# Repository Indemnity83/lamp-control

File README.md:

# ESPHome Reading Lamp (Lamp Control)

This project is a custom **ESP8266 (ESP-12E) + ESPHome retrofit** for a standard touch‑controlled bedside reading lamp, adding full **Wi‑Fi control and Home Assistant integration**.

Originally built for a fun (and slightly devious) bedtime automation, it’s now a clean, reusable **smart‑lamp controller** with both **open hardware** and **open firmware**.

Same lamp on the outside.  
Entirely new personality on the inside.

---

## ✨ Features

- ESP8266 / ESP‑12E based Wi‑Fi control  
- ESPHome firmware  
- Home Assistant native API integration  
- Smooth transitions and dimming  
- Designed to replace a stock capacitive touch controller  
- Brightness memory across power loss  
- Physical touch control + full network control

---

## 🗂️ Repository Structure

- `firmware/` – ESPHome configuration and device logic  
- `hardware/` – KiCad schematic, PCB, and mechanical assets  
- `docs/` – Rendered schematic and board images

---

## 🧠 Hardware Overview

The controller is built around a simple, low‑voltage architecture composed of four primary building blocks:

1. **Micro — ESP8266 Wi‑Fi Module (ESP‑12E)**  
   Provides all network connectivity, ESPHome firmware execution, and integration with Home Assistant.

2. **Mosfet — BSS138 MOSFET‑Based DC Dimmer Stage**  
   Handles low‑side PWM dimming of the 12V lamp load in a safe, fully low‑voltage design (no mains switching).

3. **Power — AMS1117‑3.3 Linear Voltage Regulator**  
   Steps the incoming 12V DC down to a stable 3.3V rail for the ESP8266 and logic circuitry.

4. **Touch — TTP223 Capacitive Touch Sensor**  
   Provides the physical touch interface for on/off control and brightness stepping without any mechanical switches.

### Schematic

### PCB Render

---

## 🏭 Manufacturing Assets

All fabrication outputs are generated from KiCad using the supplied Makefile:

```sh
make build
```

This generates, into the `hardware/build/` directory:

- Gerber files  
- Drill files  
- BOM (CSV)  
- Pick‑and‑place  
- PDF schematic

Manufacturing assets are also published as **GitHub Releases** and workflow artifacts.

### 🟣 Order a Pre‑Fab PCB (OSH Park)

If you prefer to skip fabrication setup and order the board directly, the exact PCB is available as a shared OSH Park project:

https://oshpark.com/shared_projects/FYbiIZpP

---

## 🧰 Bill of Materials (BOM) — Summary

This project retrofits a **touch‑controlled 12V DC bedside reading lamp** with a custom ESP8266 controller.

### 🪔 Base Lamp

- Touch‑control bedside reading lamp (original retail unit)  
- Any similar **12V capacitive‑touch lamp with an internal controller** can be adapted; however, the **PCB outline and mounting points are specifically designed for [this exact lamp model](https://a.co/d/2ksPzuO)**

> ⚠️ **USB Charging Port Note**  
> The original lamp’s built-in USB charging port will be **non-functional after this retrofit**. Supporting a protected 5V USB output (with proper current limiting and fault protection) was intentionally left **out of scope** to keep the board simple and safe.  
>  
> If you would like to restore USB charging, the recommended approach is to use a small, dedicated **12V → 5V buck converter module** and reuse the lamp’s original USB connector:  
> 1. Install a 12V → 5V buck converter module and connect the lamp’s 12V supply to the module’s input.  
> 2. **Remove the USB connector from the buck converter module** so you can access its 5V and GND output pads directly.  
> 3. Solder the original USB wiring to the 5V and GND output pads on the buck converter module, effectively feeding the original USB jack from the new 5V supply.  
>  
> Example module: https://a.co/d/jlBtOT4

> ♻️ **Salvage & Reuse Note**  
> The **spring contact** that connects the original lamp PCB to the outer plastic touch surface is **re‑used in this design**. Be sure to **pull and transfer this spring from the original board** when installing the new controller.
> 
> You can also optionally **salvage the following components from the original lamp PCB** to reduce parts sourcing:
> - The **MOSFET** (dimmer switch)
> - The tiny **22pF capacitor** used to decouple the touch spring
> - **Reverse‑polarity protection diode** (SS14‑class)
> 
> Salvaging these parts is optional but can simplify sourcing and keep e‑waste down.

### 🧠 Core Electronics

- **U3 — ESP‑12E / ESP8266 Wi‑Fi module**
- **U4 — TTP223‑BA6 capacitive touch sensor**
- **Q2 — BSS138 MOSFET** (low‑side PWM dimming)
- **U2 — AMS1117‑3.3 voltage regulator**
- **D1 — SS14 Schottky diode** (power protection)
- Decoupling and timing capacitors (C3–C7)
- Pull‑ups and current‑limit resistors (R3–R8)

---

## 🧑‍💻 Firmware

The device firmware is written in **ESPHome** and provides:

- Touch input handling via TTP223B capacitive IC  
- Brightness stepping with persistent memory  
- Long‑press physical power‑off  
- OTA updates and Home Assistant API integration

Firmware configuration files live in:

```
firmware/
```

---

## ⚡ Typical Use Cases

- Smart bedside reading lamps  
- Bedtime automations  
- Wake‑up fade lighting  
- General ESPHome‑controlled lighting

---

## 📄 License

This project uses **dual licensing**:

- **Firmware & configuration:** MIT License  
- **Hardware designs & mechanical files:** CERN Open Hardware License v2 – Permissive (CERN‑OHL‑P)

See the respective `LICENSE.md` files for full terms.

---

## ❤️ Why This Exists

Because sometimes the right solution to:

> “They’re still reading at 10 PM…”

is:

> “Fine. We’ll let the robots handle it.”

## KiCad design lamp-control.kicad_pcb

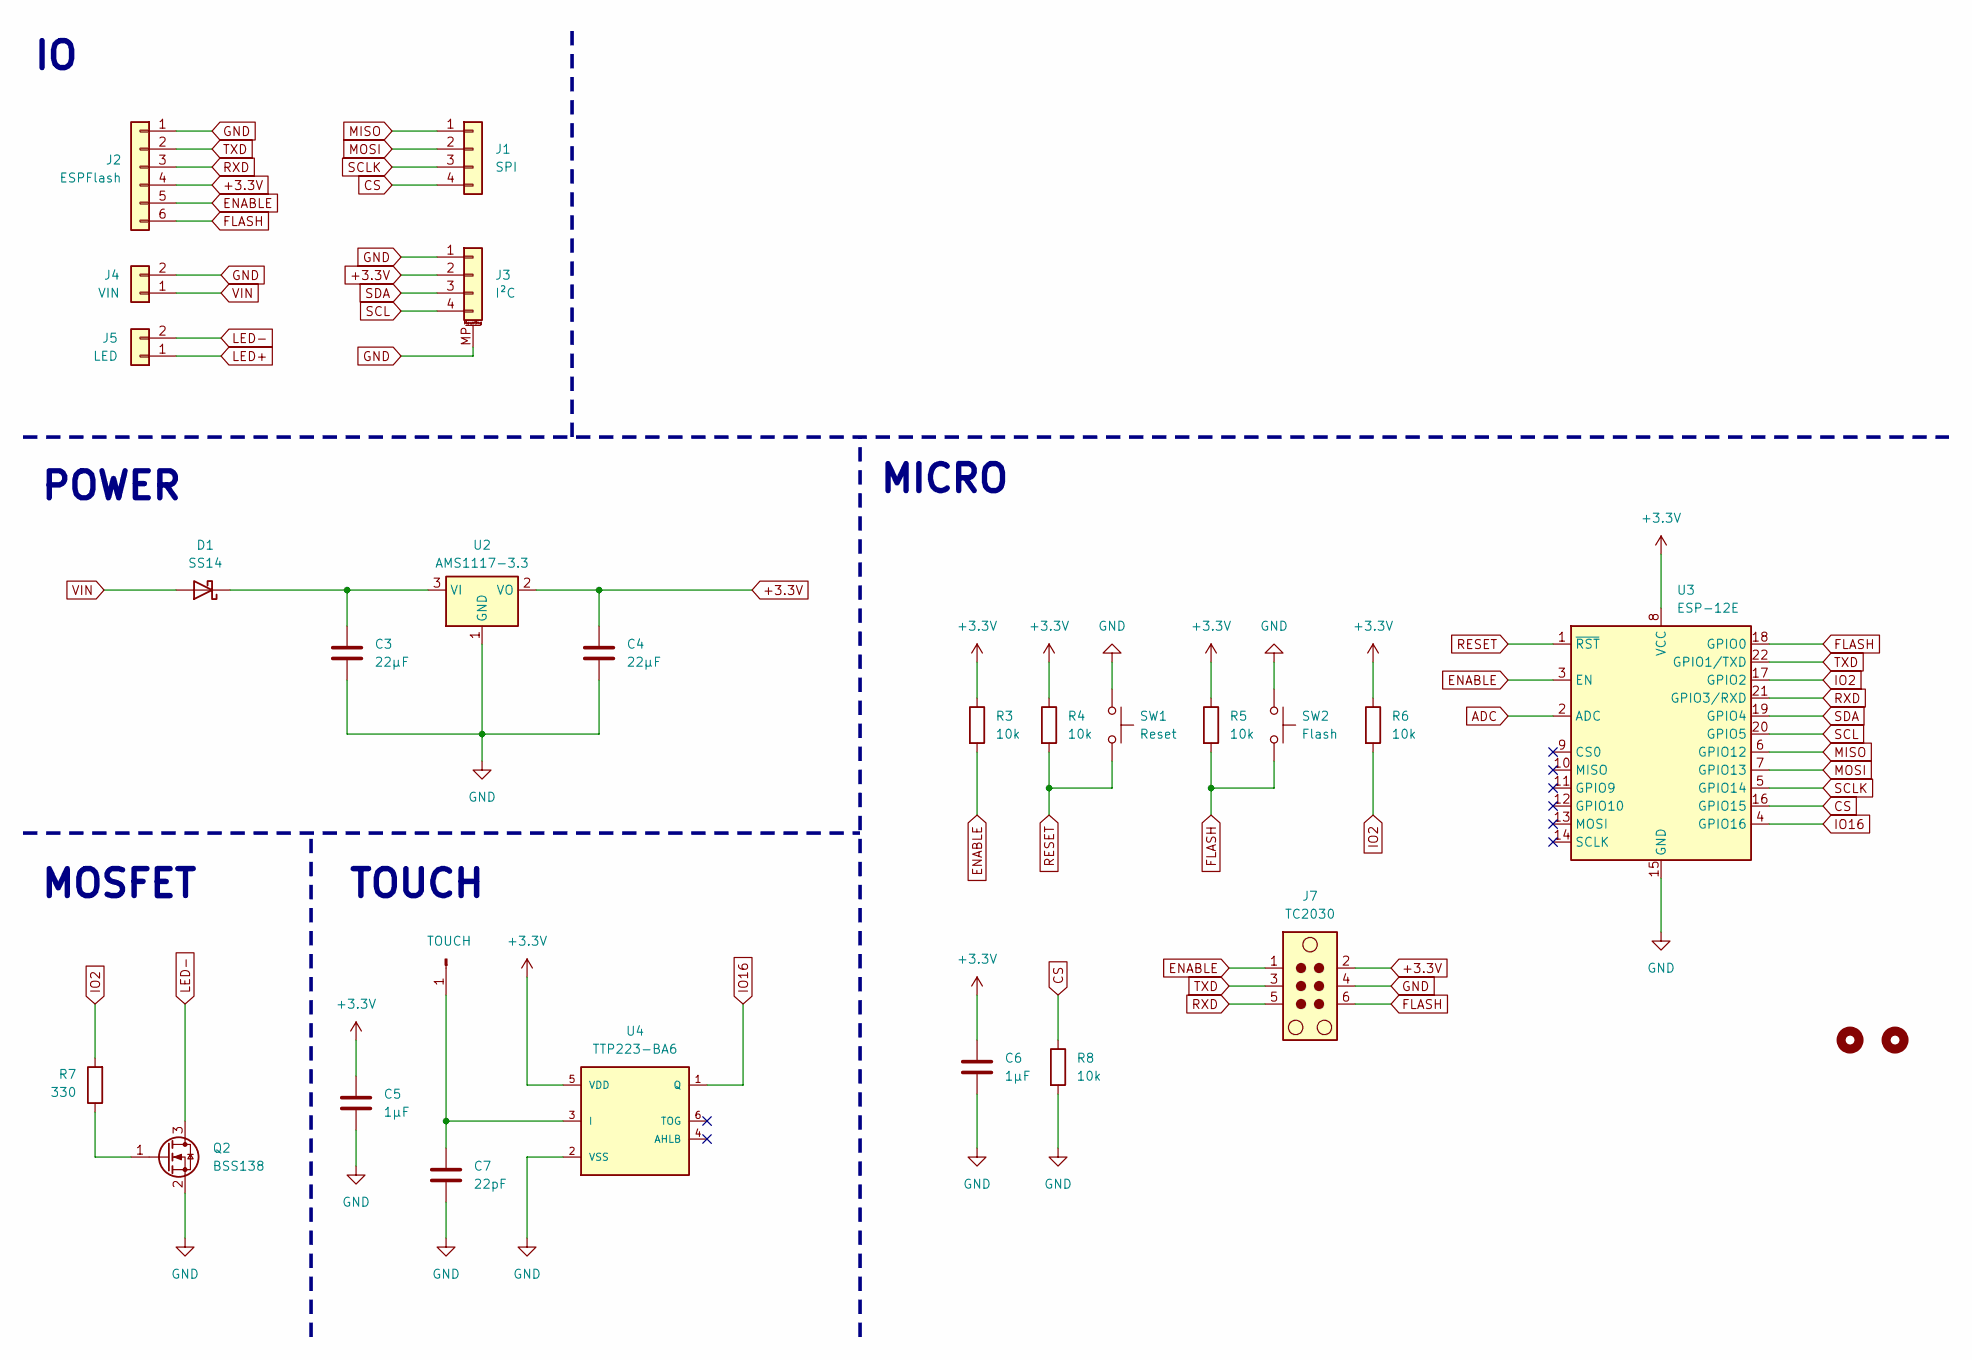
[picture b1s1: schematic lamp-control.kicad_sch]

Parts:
C3, C4: 22µF; CP_EIA-3528-12_Kemet-T_HandSolder
C5, C6: 1µF; C_0805_2012Metric_Pad1.18x1.45mm_HandSolder
C7: 22pF; C_0603_1608Metric_Pad1.08x0.95mm_HandSolder
D1: SS14; D_SMA
H1, H2: MountingHole; MountingHole_3.2mm_M3
J1: SPI; PinHeader_1x04_P2.54mm_Horizontal
J2: ESPFlash; PinHeader_1x06_P2.54mm_Horizontal
J3: I²C; JST_SH_SM04B-SRSS-TB_1x04-1MP_P1.00mm_Horizontal
J4: VIN; TerminalBlock_4Ucon_1x02_P3.50mm_Horizontal
J5: LED; TerminalBlock_4Ucon_1x02_P3.50mm_Horizontal
J6: TOUCH; SolderWire-0.5sqmm_1x01_D0.9mm_OD2.1mm
J7: TC2030; Tag-Connect_TC2030-IDC-NL_2x03_P1.27mm_Vertical
Q2: BSS138; SOT-23
R3, R4, R5, R6, R8: 10k; R_0805_2012Metric_Pad1.20x1.40mm_HandSolder
R7: 330; R_0805_2012Metric_Pad1.20x1.40mm_HandSolder
SW1: Reset; SW_Tactile_SPST_NO_Straight_CK_PTS636Sx25SMTRLFS
SW2: Flash; SW_Tactile_SPST_NO_Straight_CK_PTS636Sx25SMTRLFS
U2: AMS1117-3.3; SOT-223-3_TabPin2
U3: ESP-12E
U4: TTP223-BA6; SOT-23-6

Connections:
+3.3V: C4.1, C5.1, C6.1, J2.4, J3.2, J7.2, R3.1, R4.1, R5.1, R6.1, U2.2 (VO), U3.8 (VCC), U4.5 (VDD)
ADC: U3.2 (ADC)
CS: J1.4, R8.1, U3.16 (GPIO15)
ENABLE: J2.5, J7.1, R3.2, U3.3 (EN)
FLASH: J2.6, J7.6, R5.2, SW2.2, U3.18 (GPIO0)
GND: C3.2, C4.2, C5.2, C6.2, C7.1, J2.1, J3.1, J3.MP (MountPin), J4.2, J7.4, Q2.2 (S), R8.2, SW1.1, SW2.1, U2.1 (GND), U3.15 (GND), U4.2 (VSS)
IO2: R6.2, R7.2, U3.17 (GPIO2)
IO16: U3.4 (GPIO16), U4.1 (Q)
LED+: J5.1
LED-: J5.2, Q2.3 (D)
MISO: J1.1, U3.6 (GPIO12)
MOSI: J1.2, U3.7 (GPIO13)
unnamed: C3.1, D1.1 (K), U2.3 (VI)
unnamed: C7.2, J6.1, U4.3 (I)
unnamed: Q2.1 (G), R7.1
RESET: R4.2, SW1.2, U3.1 (~RST)
RXD: J2.3, J7.5, U3.21 (GPIO3/RXD)
SCL: J3.4, U3.20 (GPIO5)
SCLK: J1.3, U3.5 (GPIO14)
SDA: J3.3, U3.19 (GPIO4)
TXD: J2.2, J7.3, U3.22 (GPIO1/TXD)
VIN: D1.2 (A), J4.1

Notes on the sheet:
MICRO
TOUCH
POWER
MOSFET

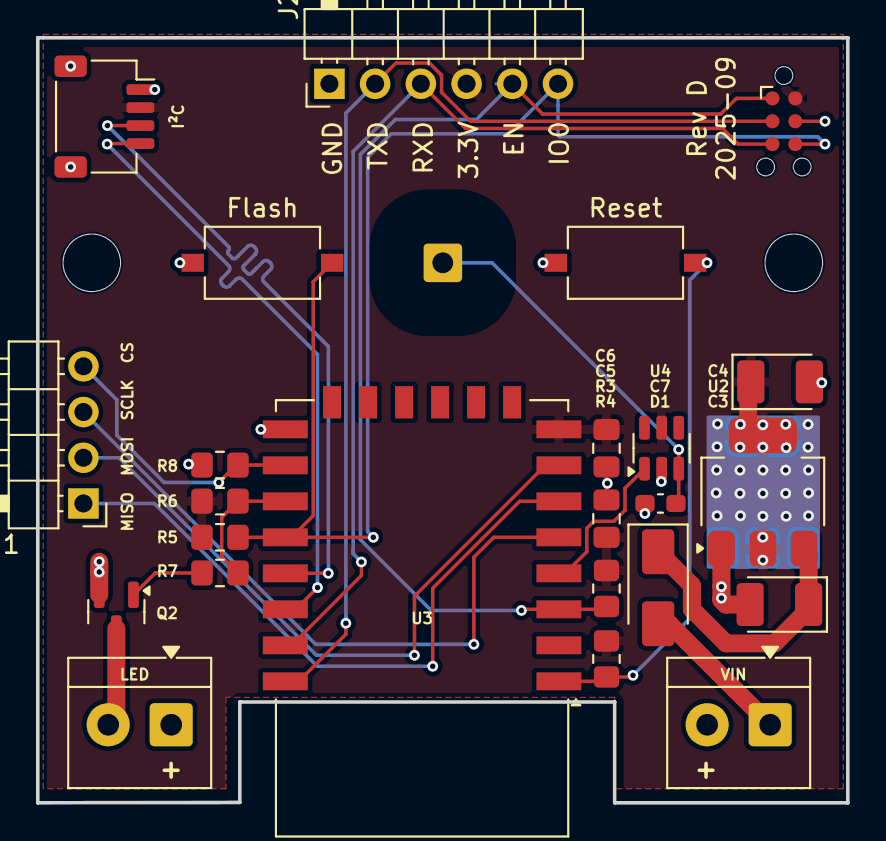
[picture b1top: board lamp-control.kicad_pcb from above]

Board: 2 copper layers, 45.0 x 42.5 mm, 27 parts (0 on the bottom side), 20 nets.

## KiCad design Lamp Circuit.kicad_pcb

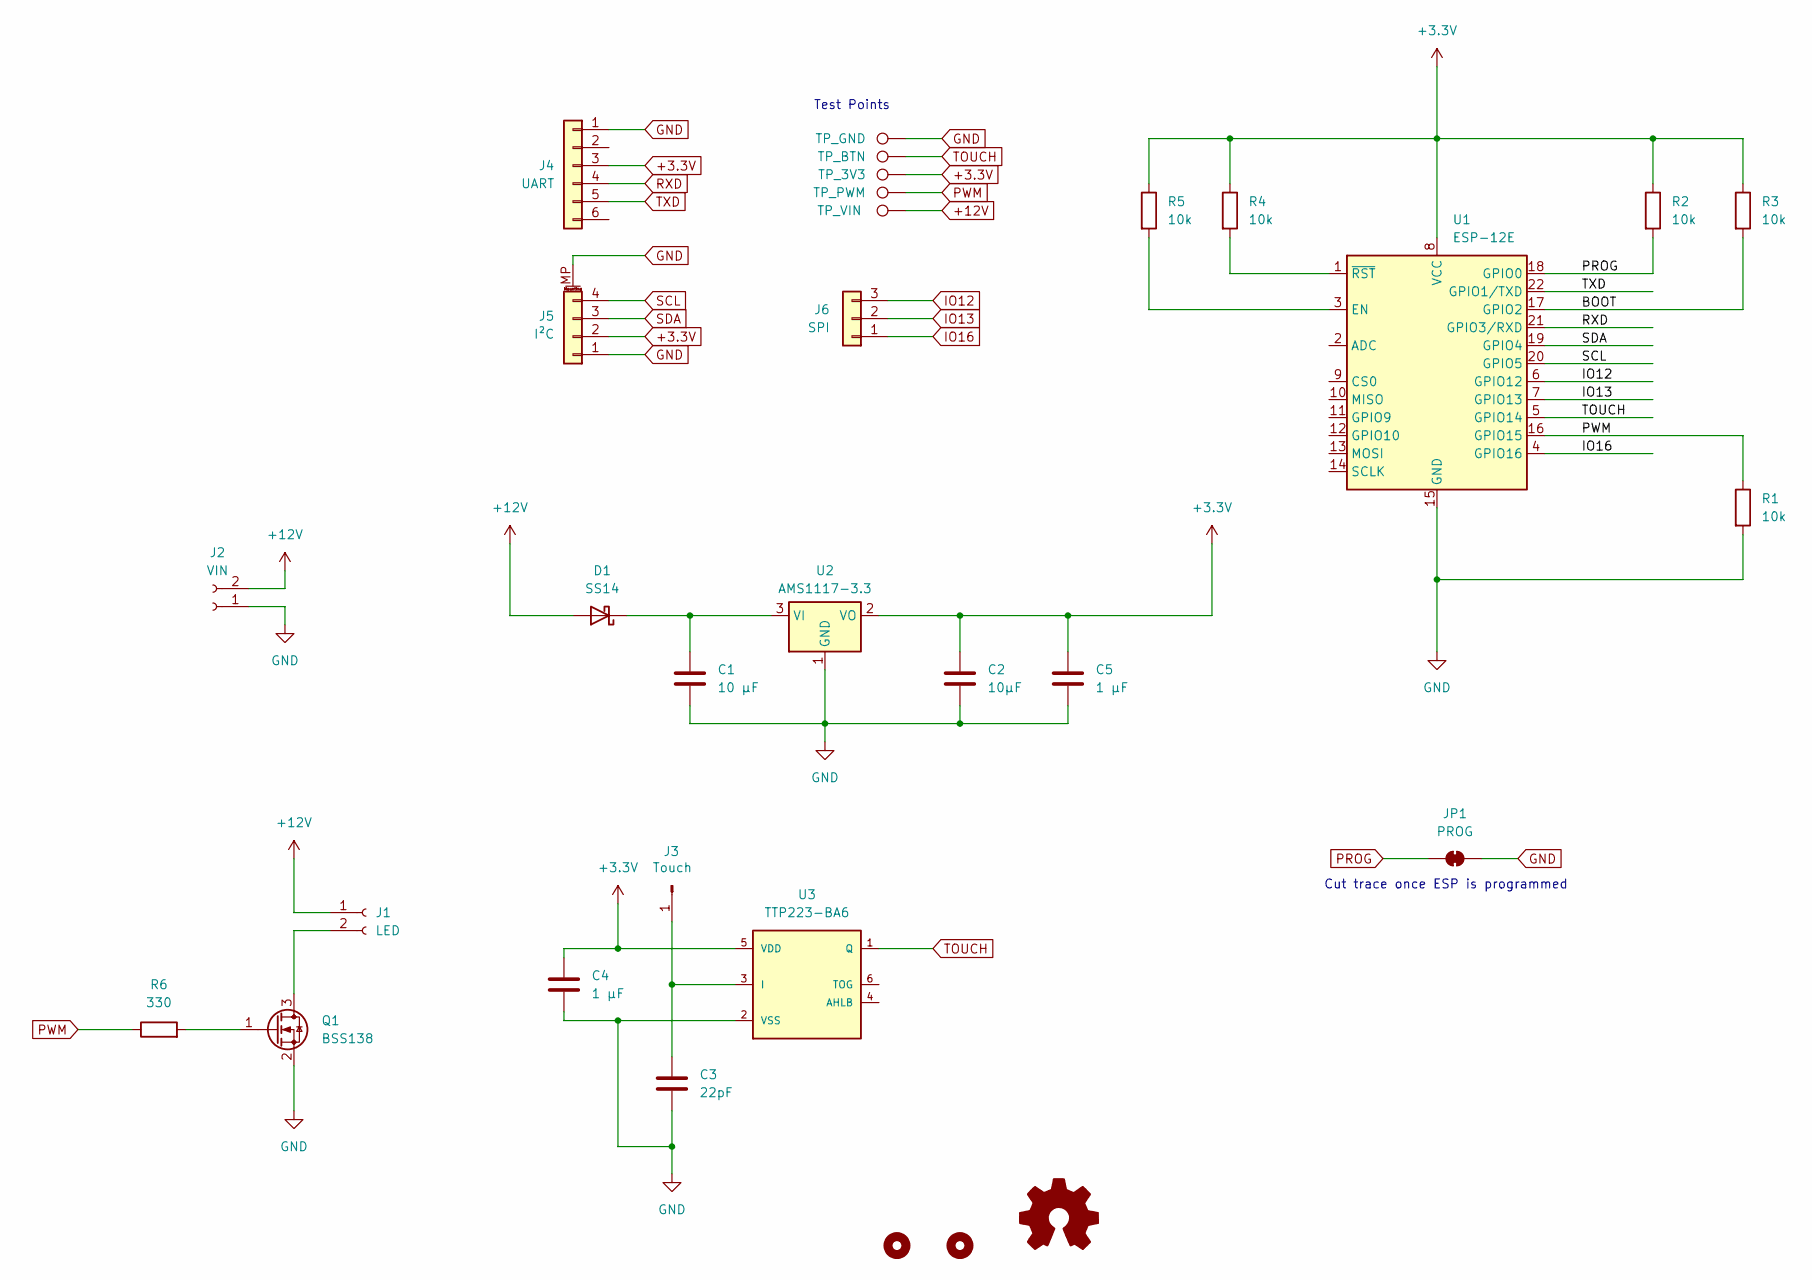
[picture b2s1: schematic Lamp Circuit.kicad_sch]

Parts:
C1: 10 µF; C_0805_2012Metric_Pad1.18x1.45mm_HandSolder
C2: 10µF; C_0805_2012Metric_Pad1.18x1.45mm_HandSolder
C3: 22pF; C_0805_2012Metric_Pad1.18x1.45mm_HandSolder
C4, C5: 1 µF; C_0805_2012Metric_Pad1.18x1.45mm_HandSolder
D1: SS14; D_SMA
H1, H2: MountingHole; MountingHole_3.2mm_M3
J1: LED; TerminalBlock_4Ucon_1x02_P3.50mm_Horizontal
J2: VIN; TerminalBlock_4Ucon_1x02_P3.50mm_Horizontal
J3: Touch; SolderWire-0.5sqmm_1x01_D0.9mm_OD2.1mm
J4: UART; PinHeader_1x06_P2.54mm_Vertical
J5: I²C; JST_SH_SM04B-SRSS-TB_1x04-1MP_P1.00mm_Horizontal
J6: SPI; SolderWire-0.1sqmm_1x03_P3.6mm_D0.4mm_OD1mm
JP1: PROG; SolderJumper-2_P1.3mm_Bridged_RoundedPad1.0x1.5mm
Q1: BSS138; SOT-23
R1, R2, R3, R4, R5: 10k; R_0805_2012Metric_Pad1.20x1.40mm_HandSolder
R6: 330; R_0805_2012Metric_Pad1.20x1.40mm_HandSolder
TP1: TP_PWM; TestPoint_Pad_1.0x1.0mm
TP2: TP_BTN; TestPoint_Pad_1.0x1.0mm
TP3: TP_3V3; TestPoint_Pad_1.0x1.0mm
TP4: TP_GND; TestPoint_Pad_1.0x1.0mm
TP5: TP_VIN; TestPoint_Pad_1.0x1.0mm
U1: ESP-12E
U2: AMS1117-3.3; SOT-223-3_TabPin2
U3: TTP223-BA6; SOT-23-6

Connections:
+3.3V: C2.1, C4.1, C5.1, J4.3, J5.2, R2.1, R3.1, R4.1, R5.1, TP3.1, U1.8 (VCC), U2.2 (VO), U3.5 (VDD)
+12V: D1.2 (A), J1.1, J2.2, TP5.1
/BOOT: R3.2, U1.17 (GPIO2)
GND: C1.2, C2.2, C3.1, C4.2, C5.2, J2.1, J4.1, J5.1, J5.MP (MountPin), JP1.2 (B), Q1.2 (S), R1.2, TP4.1, U1.15 (GND), U2.1 (GND), U3.2 (VSS)
IO12: J6.3, U1.6 (GPIO12)
IO13: J6.2, U1.7 (GPIO13)
IO16: J6.1, U1.4 (GPIO16)
unnamed: C1.1, D1.1 (K), U2.3 (VI)
unnamed: J1.2, Q1.3 (D)
unnamed: C3.2, J3.1, U3.3 (I)
unnamed: Q1.1 (G), R6.2
unnamed: R5.2, U1.3 (EN)
unnamed: R4.2, U1.1 (~RST)
PROG: JP1.1 (A), R2.2, U1.18 (GPIO0)
PWM: R1.1, R6.1, TP1.1, U1.16 (GPIO15)
RXD: J4.4, U1.21 (GPIO3/RXD)
SCL: J5.4, U1.20 (GPIO5)
SDA: J5.3, U1.19 (GPIO4)
TOUCH: TP2.1, U1.5 (GPIO14), U3.1 (Q)
TXD: J4.5, U1.22 (GPIO1/TXD)

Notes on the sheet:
Cut trace once ESP is programmed
Test Points

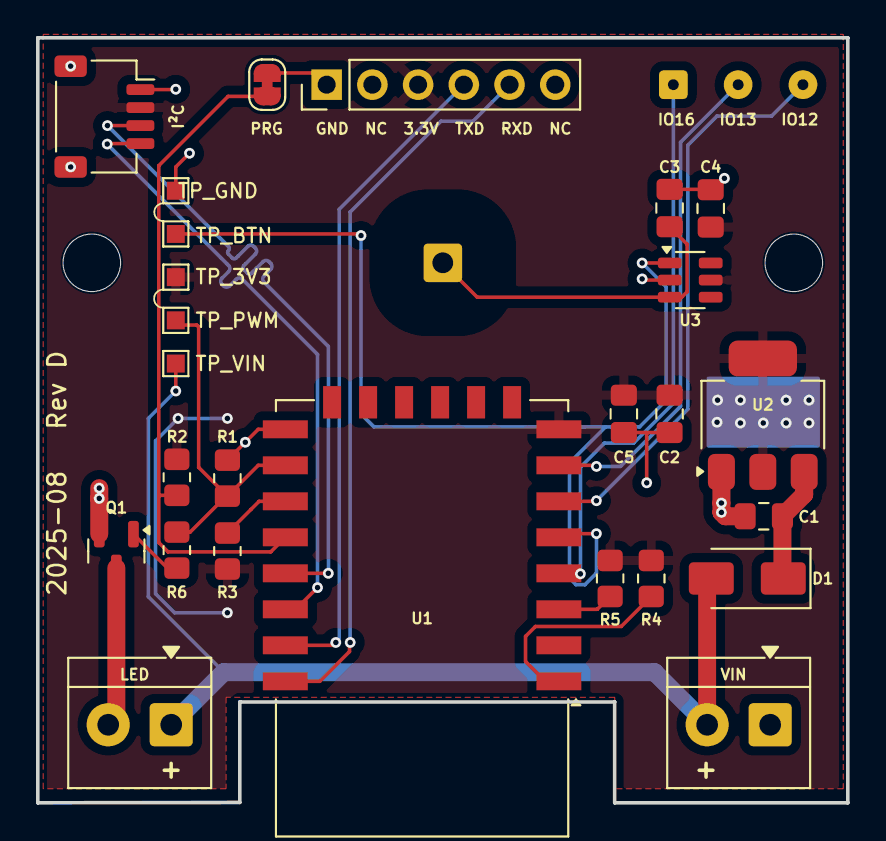
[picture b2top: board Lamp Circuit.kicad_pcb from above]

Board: 2 copper layers, 45.0 x 42.5 mm, 30 parts (0 on the bottom side), 20 nets.

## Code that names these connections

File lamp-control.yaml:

esphome:
  name: lamp-control

esp8266:
  board: esp12e

api:
  encryption:
    key: !secret api_encryption_key

ota:
  - platform: esphome
    password: !secret ota_password

wifi:
  ssid: !secret wifi_ssid
  password: !secret wifi_password
  ap:
    ssid: "${name}-${mac_suffix}"

captive_portal:

# web_server:
#   port: 80
#   # Optional: Enable for a simple web interface for diagnostics and control.
#   # Not recommended for production devices due to security concerns.

# i2c:
#   sda: GPIO4
#   scl: GPIO5
#   # Optional: Enable if you want to use I2C sensors or peripherals.

# spi:
#   clk_pin: GPIO14
#   mosi_pin: GPIO13
#   miso_pin: GPIO12
#   # Optional: Enable if you want to use SPI devices.

globals:
  - id: brightness_step
    type: int
    restore_value: no
    initial_value: '0'
    
output:
  - platform: esp8266_pwm
    pin: GPIO2
    id: lamp_pwm
    frequency: 1000 Hz

light:
  - platform: monochromatic
    id: lamp_light
    name: "Reading Lamp"
    output: lamp_pwm
    default_transition_length: 300ms
    restore_mode: ALWAYS_OFF
    gamma_correct: 2.2

binary_sensor:
  - platform: gpio
    pin:
      number: GPIO16
    internal: true
    id: touch_sensor
    on_click:
      then:
        - lambda: |-
            if (id(lamp_light).current_values.is_on()) {
              id(brightness_step) = (id(brightness_step) + 1) % 4;
            }
            static const float L[4] = {1.0f, 0.75f, 0.50f, 0.25f};
            auto call = id(lamp_light).turn_on();
            call.set_brightness(L[id(brightness_step)]);
            call.perform();
    on_multi_click:
      - timing:
          - ON for at least 1s
        then:
          - light.turn_off: lamp_light

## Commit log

2025-09-03 Rev D
2025-09-07 update capacitors for voltage regulator to improve stability
2025-09-07 add documentation and make tools
2025-09-07 add esphome config
2025-09-07 Simplify design (#1)
2025-09-07 install full kicad on build
2025-12-09 Update design files
2025-12-09 Speed up build workflow by caching KiCad APT packages
